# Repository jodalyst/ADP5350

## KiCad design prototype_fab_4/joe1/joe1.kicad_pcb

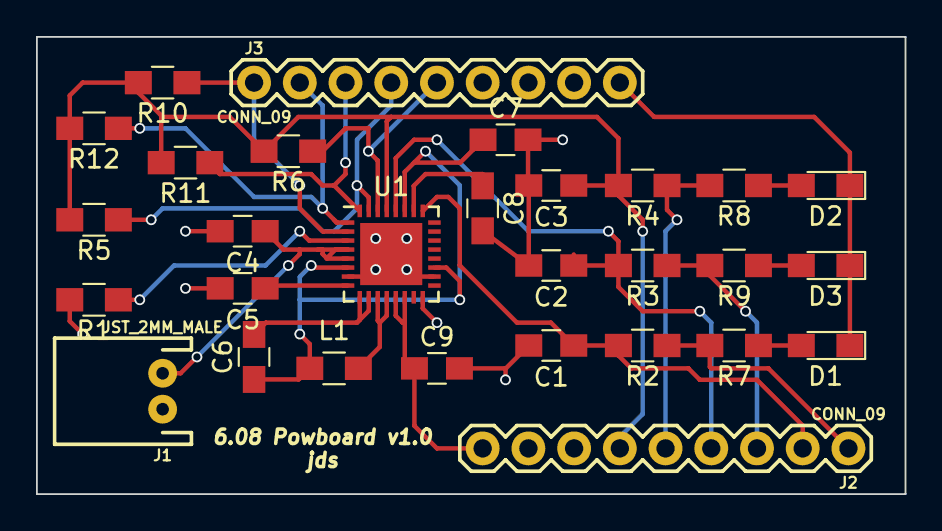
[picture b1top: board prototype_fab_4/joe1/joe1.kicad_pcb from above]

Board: 2 copper layers, 48.3 x 25.4 mm, 29 parts (0 on the bottom side), 24 nets.

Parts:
C1, C2, C3, C7: 1u; C_0805_HandSoldering
C4, C6: 10u; C_0805_HandSoldering
C5: 4.7u; C_0805_HandSoldering
C8, C9: 2.2u; C_0805_HandSoldering
D1, D2, D3: LED; LED_0805_HandSoldering
J1: JST_2MM_MALE; JST-2-PTH
J2, J3: CONN_09; 1X09
L1: 1.5u; L_0805_HandSoldering
R1: 47K; R_0805_HandSoldering
R2, R3, R4: 0.5; R_0805_HandSoldering
R5, R6, R7, R8, R9, R10, R11, R12: 4.7k; R_0805_HandSoldering
U1: ADP5350; QFN-32-1EP_5x5mm_Pitch0.5mm

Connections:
GND: C1.2, C2.2, C3.2, C4.2, C5.2, C7.2, C8.2, C9.2, J1.1, J2.7, J2.8, J3.6, R1.2, U1.7, U1.16, U1.18, U1.33
unnamed: C1.1, J2.2, R2.2, U1.25
unnamed: C2.1, J2.4, R3.2, U1.28
unnamed: C3.1, J2.6, R4.2, R5.2, R6.2, R10.2, R11.2, R12.2, U1.29
unnamed: C4.1, J1.2, U1.4, U1.5
unnamed: C5.1, U1.8
unnamed: C6.1, C7.1, L1.1, U1.6, U1.19, U1.27
unnamed: C6.2, U1.9, U1.10
unnamed: C8.1, U1.26
unnamed: D1.1, D2.1, D3.1, J3.9
unnamed: D1.2, R7.1
unnamed: D2.2, R8.1
unnamed: D3.2, R9.1
unnamed: J2.1, R2.1, R7.2
unnamed: J2.3, R3.1, R9.2
unnamed: J2.5, R4.1, R8.2
unnamed: J3.1, R10.1, U1.2
unnamed: J3.2, R12.1, U1.1
unnamed: J3.3, R11.1, U1.32
unnamed: J3.4, R5.1, U1.31
unnamed: J3.5, R6.1, U1.30
unnamed: L1.2, U1.11, U1.12
unnamed: R1.1, U1.3
VCC: C9.1, J2.9, U1.13, U1.14

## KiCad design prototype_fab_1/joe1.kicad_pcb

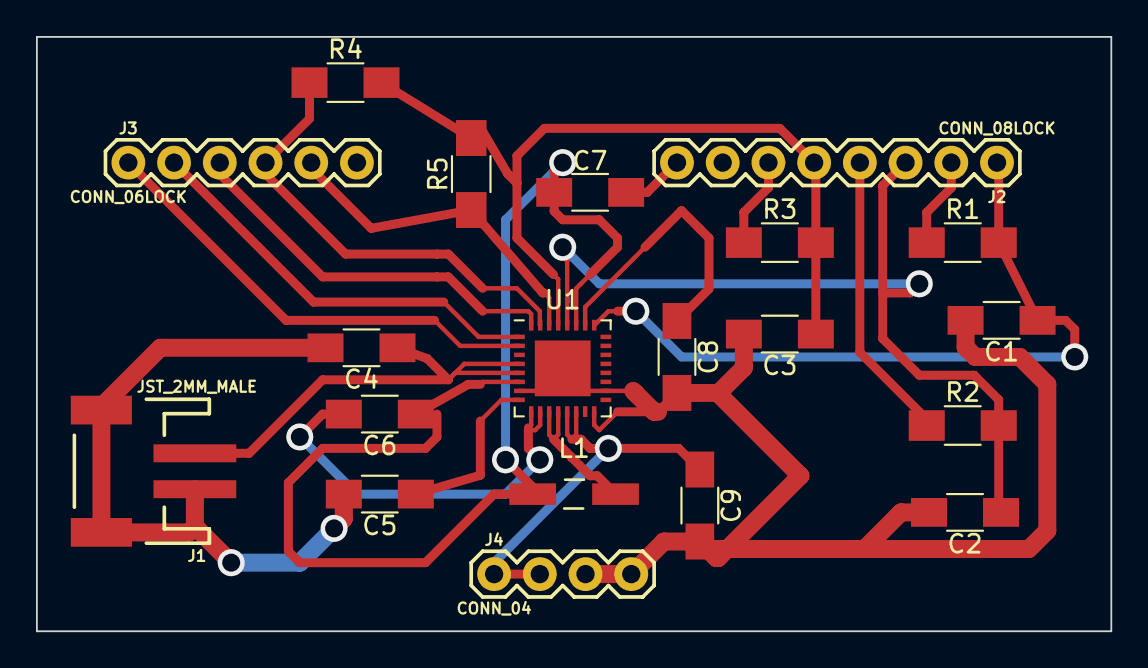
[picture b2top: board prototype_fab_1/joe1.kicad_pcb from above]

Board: 2 copper layers, 59.7 x 33.0 mm, 20 parts (0 on the bottom side), 19 nets.

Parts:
C1, C2, C3, C7: 1u; C_1206_HandSoldering
C4, C6: 10u; C_1206_HandSoldering
C5: 4.7u; C_1206_HandSoldering
C8, C9: 2.2u; C_1206_HandSoldering
J1: JST_2MM_MALE; JST-2-SMD
J2: CONN_08LOCK; 1X08
J3: CONN_06LOCK; 1X06
J4: CONN_04; 1X04
L1: 1.5u; Choke_SMD_1206_Handsoldering
R1, R2, R3: 0.5; R_1206_HandSoldering
R4, R5: 4.7k; R_1206_HandSoldering
U1: ADP5350; WQFN-32-1EP_5x5mm_Pitch0.5mm

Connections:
GND: C1.2, C2.2, C3.2, C4.2, C5.2, C7.2, C8.2, C9.2, J1.1, J1.NC1, J1.NC2, J2.7, J2.8, J3.6, J4.3, J4.4, U1.7, U1.16, U1.18, U1.33
unnamed: C1.1, J2.1, R1.2, U1.25
unnamed: C2.1, J2.3, R2.2, U1.28
unnamed: C3.1, J2.5, R3.2, R4.2, R5.2, U1.29
unnamed: C4.1, J1.2, U1.4, U1.5
unnamed: C5.1, U1.8
unnamed: C6.1, C7.1, L1.1, U1.6, U1.27
unnamed: C6.2, U1.9, U1.10
unnamed: C8.1, U1.26
unnamed: J2.2, R1.1
unnamed: J2.4, R2.1
unnamed: J2.6, R3.1
unnamed: J3.1, U1.2
unnamed: J3.2, U1.1
unnamed: J3.3, U1.32
unnamed: J3.4, R4.1, U1.31
unnamed: J3.5, R5.1, U1.30
unnamed: L1.2, U1.11, U1.12
VCC: C9.1, J4.1, J4.2, U1.13, U1.14

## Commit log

2017-09-26 initial commit on library
2017-09-26 updating example junk sketch
2017-09-26 adjusting so the name is right
2017-09-26 adding in some register addresses
2017-09-26 updating library...LDO enable
2017-09-26 updating batter ldo control...still wrong
2017-09-26 updating source
2017-09-26 adding in two heartbeat things
2017-10-09 Just a few declaration errors that were corrected. The example code is completely functional.
2017-10-09 Added comments
2017-10-25 Fixed small bug(s) regarding LDO control. Added functionality to control the voltage output of LDOs.
2017-11-03 Added the KiCad devboard for the ADP5350
    LDOs 1-3 have the voltage divider circuit. Didn't remember which resistor values to use so I just said 40K for the dividing and 1 Ohm for the current sense
    Could not find anything appropriate to create the switches so left them blank for the time being
    Have not started the physical board layout yet
2017-11-06 Replaced switches with wires and changed resistor values to 10K Ohms
2017-11-08 Mapped schematic parts to footprints for PCB. Size of L/R/C footprints -> 1206
    Simplified some circuitry for the sake of sizing and uneeded parts.
    Changed test points out with individual parts.
    2 errors in electrical rules/connectivity testing ignored (not important)
2017-12-03 moving files and updating test file
2017-12-03 changing name to something reasonable.
2017-12-04 adding in kicad stuff for testing/prototyping
2017-12-05 new files for fab submissionl
2017-12-07 updating adp example script...started working on lab around int
2017-12-14 adding in new fab and update library
2017-12-15 updating example for ldo
2017-12-18 adding in new design layer
2017-12-22 redoing library with pin 33
2018-01-10 adding in minor changes for ESP32 compatibility
2018-01-10 adding in battery tracking example
2018-01-12 adding oled example, experiment
2018-01-12 adding in the newest version of hte ADPboard, with BOM, etc...) .
